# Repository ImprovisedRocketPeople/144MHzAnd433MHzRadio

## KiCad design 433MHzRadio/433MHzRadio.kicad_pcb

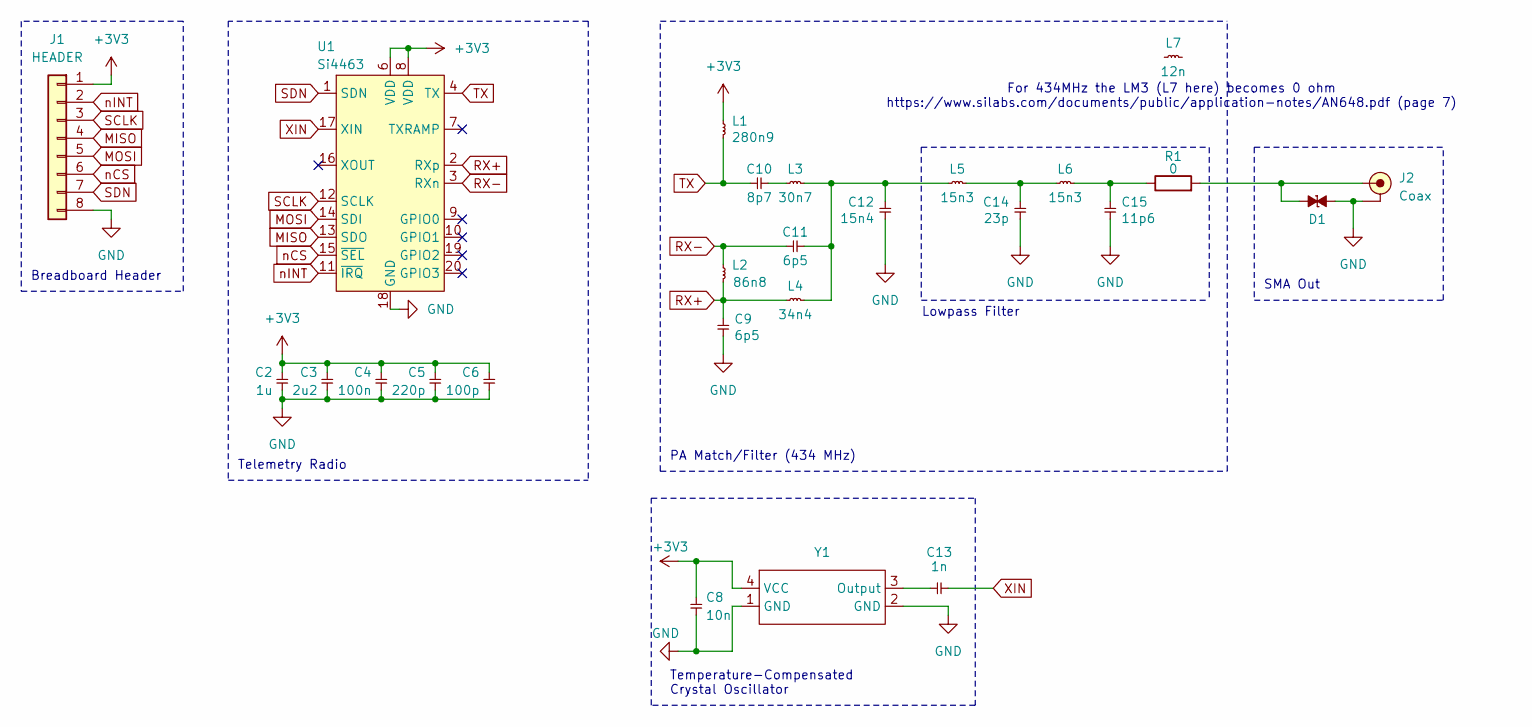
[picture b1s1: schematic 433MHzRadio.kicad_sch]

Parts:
C2: 1u; C_0402_1005Metric_Pad0.74x0.62mm_HandSolder; Farnell 9402063
C3: 2u2; C_0402_1005Metric_Pad0.74x0.62mm_HandSolder; Farnell 2672111
C4: 100n; C_0402_1005Metric_Pad0.74x0.62mm_HandSolder; Farnell 9402047
C5: 220p; C_0402_1005Metric_Pad0.74x0.62mm_HandSolder; Farnell 3019240
C6: 100p; C_0402_1005Metric_Pad0.74x0.62mm_HandSolder; Farnell 2906905
C8: 10n; C_0402_1005Metric_Pad0.74x0.62mm_HandSolder; Farnell 9402047
C9: 6p5; C_0402_1005Metric_Pad0.74x0.62mm_HandSolder; Farnell 1758933
C10: 8p7; C_0402_1005Metric_Pad0.74x0.62mm_HandSolder; Farnell 2781439
C11: 6p5; C_0402_1005Metric_Pad0.74x0.62mm_HandSolder; Farnell 3369062
C12: 15n4; C_0402_1005Metric_Pad0.74x0.62mm_HandSolder; Farnell 2627370
C13: 1n; C_0402_1005Metric_Pad0.74x0.62mm_HandSolder; Farnell 2332520
C14: 23p; C_0402_1005Metric_Pad0.74x0.62mm_HandSolder; Farnell 3013357
C15: 11p6; C_0402_1005Metric_Pad0.74x0.62mm_HandSolder; Farnell 3013357
D1: D_ESD; D_0402_1005Metric_Pad0.77x0.64mm_HandSolder; Farnell 2368169
J1: HEADER; Header_Breadboard_1x08; Farnell 1022256
J2: Coax; SMA-Edge; Farnell 1608592
L1: 280n9; L_0402_1005Metric_Pad0.77x0.64mm_HandSolder; Farnell 3471254
L2: 86n8; L_0402_1005Metric_Pad0.77x0.64mm_HandSolder; Farnell 1343084
L3: 30n7; L_0402_1005Metric_Pad0.77x0.64mm_HandSolder; Farnell 1343068
L4: 34n4; L_0402_1005Metric_Pad0.77x0.64mm_HandSolder; Farnell 3263549
L5: 15n3; L_0402_1005Metric_Pad0.77x0.64mm_HandSolder; Farnell 1343082
L6: 15n3; L_0402_1005Metric_Pad0.77x0.64mm_HandSolder; Farnell 3263549
L7: 12n; L_0402_1005Metric_Pad0.77x0.64mm_HandSolder; Farnell 1343082
R1: 0; R_0402_1005Metric_Pad0.72x0.64mm_HandSolder
U1: Si4463; QFN-20_L4.0-W4.0-P0.50-TL-EP2.5
Y1: 26MHz; CRYSTAL-SMD_4P-L2.5-W2.0-BL-1; Manufacturer Part 2T026000VY; LCSC Part Name 26MHz ±0.5ppm 1.8V~3.3V

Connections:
+3V3: C2.1, C3.1, C4.1, C5.1, C6.1, C8.1, J1.1, L1.1, U1.6 (VDD), U1.8 (VDD), Y1.4 (VCC)
GND: C2.2, C3.2, C4.2, C5.2, C6.2, C8.2, C9.2, C12.2, C14.2, C15.2, D1.2, J1.8, J2.2 (GND), U1.18 (GND), U1.21 (GND), Y1.1 (GND), Y1.2 (GND)
MISO: J1.4, U1.13 (SDO)
MOSI: J1.5, U1.14 (SDI)
unnamed: C10.2, L3.1
unnamed: C11.2, C12.1, L3.2, L4.2, L5.1
unnamed: C14.1, L5.2, L6.1
unnamed: C15.1, L6.2, R1.1
unnamed: D1.1, J2.1 (RF), R1.2
unnamed: C13.1, Y1.3 (Output)
RX+: C9.1, L2.2, L4.1, U1.2 (RXp)
RX-: C11.1, L2.1, U1.3 (RXn)
SCLK: J1.3, U1.12 (SCLK)
SDN: J1.7, U1.1 (SDN)
TX: C10.1, L1.2, U1.4 (TX)
XIN: C13.2, U1.17 (XIN)
nCS: J1.6, U1.15 (~SEL)
nINT: J1.2, U1.11 (~IRQ)

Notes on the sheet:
Temperature-Compensated Crystal Oscillator
SMA Out
Lowpass Filter
For 434MHz the LM3 (L7 here) becomes 0 ohm https://www.silabs.com/documents/public/application-notes/AN648.pdf (page 7)
PA Match/Filter (434 MHz)
Breadboard Header
Telemetry Radio

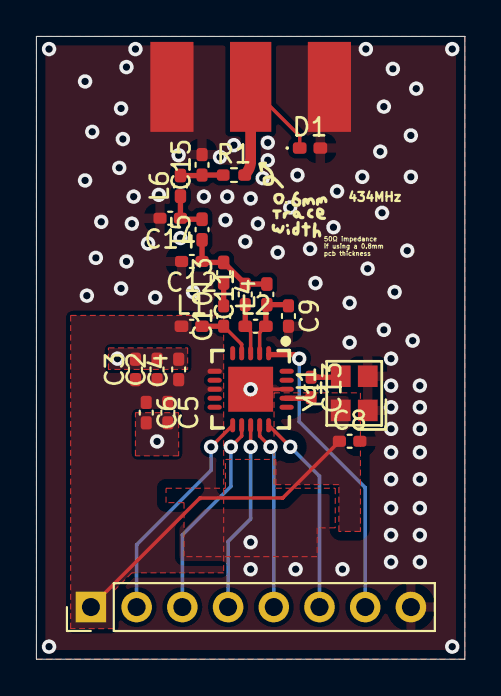
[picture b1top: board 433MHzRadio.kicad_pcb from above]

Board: 2 copper layers, 23.8 x 34.6 mm, 25 parts (0 on the bottom side), 18 nets.

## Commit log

2025-05-08 844MHz test board rn
2025-05-10 Changed proejct name and finishe the 434MHz radio pcb
